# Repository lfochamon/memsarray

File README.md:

# MEMSArray: A prototype MEMS microphone array for the BeagleBone Black

This repository contains a prototype MEMS microphone array cape for the BBB.

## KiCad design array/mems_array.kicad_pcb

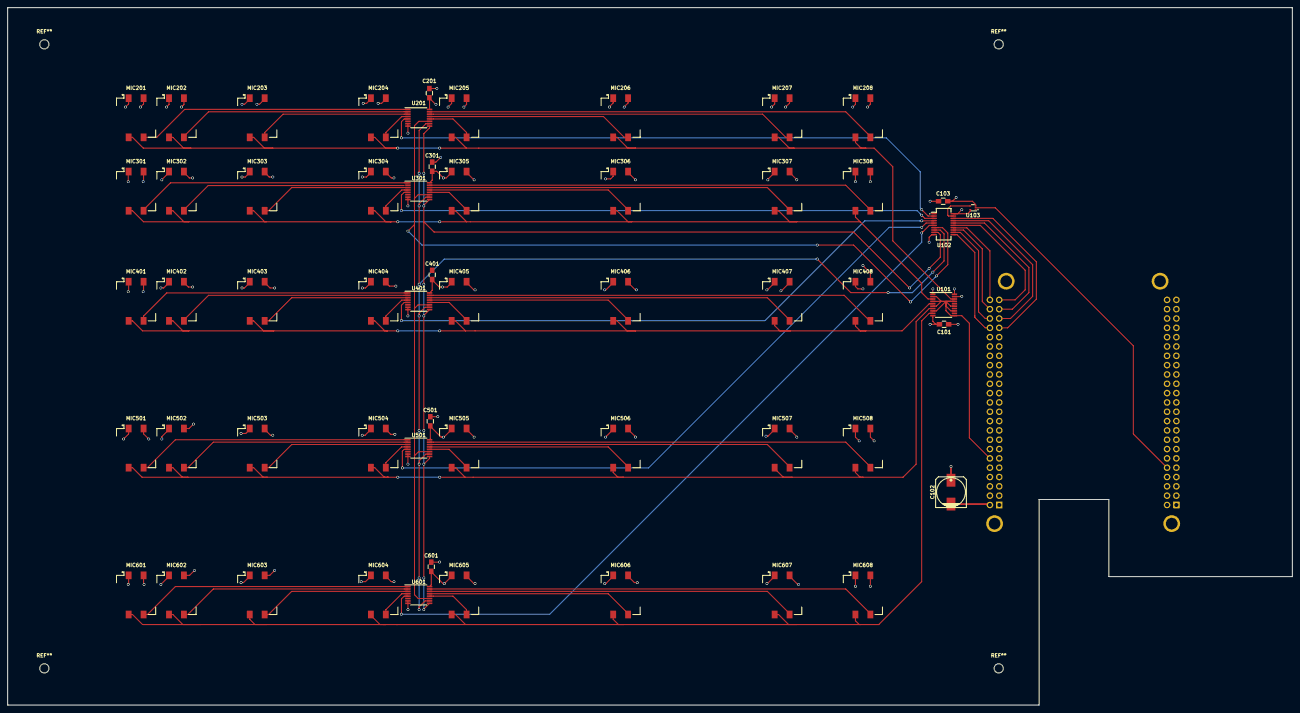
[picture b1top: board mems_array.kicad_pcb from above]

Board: 4 copper layers, 350.0 x 190.0 mm, 57 parts (1 on the bottom side), 66 nets.

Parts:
C101, C103, C201, C301, C401, C501, C601: 1uF; C_0805_HandSoldering
C102: 100uF; c_elec_8x10
MIC201, MIC202, MIC203, MIC204, MIC205, MIC206, MIC207, MIC208, MIC301, MIC302, MIC303, MIC304, MIC305, MIC306, MIC307, MIC308, MIC401, MIC402, MIC403, MIC404, MIC405, MIC406, MIC407, MIC408, MIC501, MIC502, MIC503, MIC504, MIC505, MIC506, MIC507, MIC508, MIC601, MIC602, MIC603, MIC604, MIC605, MIC606, MIC607, MIC608: MIC_MODULE; Mems_Mic_Module
U101: 74AHC244; TSSOP-20_4.4x6.5mm_Pitch0.65mm
U102: 743245; SOP-20_600x175_Pitch0.635
U103: 741G04; SOTFL-5_160x50_Pitch0.5
U104: BEAGLEBONEBLACK; beagleboneblack
U201, U301, U401, U501, U601: SN74CTBLV3251; TSSOP-16_4.4x5mm_Pitch0.65mm

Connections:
/Microphone set A/CLK: MIC201.4, MIC202.4, MIC203.4, MIC204.4, MIC205.4, MIC206.4, MIC207.4, MIC208.4, U101.18
/Microphone set A/OUT: U102.2, U201.5
/Microphone set A/S0: U102.7, U201.11, U301.11, U401.11, U501.11, U601.11
/Microphone set A/S1: U102.8, U201.10, U301.10, U401.10, U501.10, U601.10
/Microphone set A/S2: U102.9, U201.9, U301.9, U401.9, U501.9, U601.9
/Microphone set B/CLK: MIC301.4, MIC302.4, MIC303.4, MIC304.4, MIC305.4, MIC306.4, MIC307.4, MIC308.4, U101.3
/Microphone set B/OUT: U102.3, U301.5
/Microphone set C/CLK: MIC401.4, MIC402.4, MIC403.4, MIC404.4, MIC405.4, MIC406.4, MIC407.4, MIC408.4, U101.5
/Microphone set C/OUT: U102.4, U401.5
/Microphone set D/CLK: MIC501.4, MIC502.4, MIC503.4, MIC504.4, MIC505.4, MIC506.4, MIC507.4, MIC508.4, U101.7
/Microphone set D/OUT: U102.5, U501.5
/Microphone set E/CLK: MIC601.4, MIC602.4, MIC603.4, MIC604.4, MIC605.4, MIC606.4, MIC607.4, MIC608.4, U101.9
/Microphone set E/OUT: U102.6, U601.5
/PRU0_15: U101.2, U101.4, U101.6, U101.8, U101.11, U101.13, U101.15, U101.17, U104.B12
/PRU1_0: U102.15, U104.B45
/PRU1_1: U102.14, U104.B46
/PRU1_2: U102.16, U104.B43
/PRU1_3: U102.13, U104.B44
/PRU1_4: U102.17, U104.B41
/PRU1_5: U102.12, U104.B42
/PRU1_6: U102.18, U104.B39
/PRU1_7: U102.11, U104.B40
/SYS_RESETn: U103.2, U104.C10
DGND: C101.2, C102.2, C103.2, C201.2, C301.2, C401.2, C501.2, C601.2, MIC201.2, MIC202.2, MIC203.2, MIC204.2, MIC205.2, MIC206.2, MIC207.2, MIC208.2, MIC301.2, MIC302.2, MIC303.2, MIC304.2, MIC305.2, MIC306.2, MIC307.2, MIC308.2, MIC401.2, MIC402.2, MIC403.2, MIC404.2, MIC405.2, MIC406.2, MIC407.2, MIC408.2, MIC501.2, MIC502.2, MIC503.2, MIC504.2, MIC505.2, MIC506.2, MIC507.2, MIC508.2, MIC601.2, MIC602.2, MIC603.2, MIC604.2, MIC605.2, MIC606.2, MIC607.2, MIC608.2, U101.1, U101.10, U101.19, U102.10, U103.3, U104.B1, U104.B2, U104.C1, U104.C2, U104.C43, U104.C44, U104.C45, U104.C46, U201.7, U201.8, U301.7, U301.8, U401.7, U401.8, U501.7, U501.8, U601.7, U601.8
DVDD: C101.1, C102.1, C103.1, C201.1, C301.1, C401.1, C501.1, C601.1, MIC201.1, MIC202.1, MIC203.1, MIC204.1, MIC205.1, MIC206.1, MIC207.1, MIC208.1, MIC301.1, MIC302.1, MIC303.1, MIC304.1, MIC305.1, MIC306.1, MIC307.1, MIC308.1, MIC401.1, MIC402.1, MIC403.1, MIC404.1, MIC405.1, MIC406.1, MIC407.1, MIC408.1, MIC501.1, MIC502.1, MIC503.1, MIC504.1, MIC505.1, MIC506.1, MIC507.1, MIC508.1, MIC601.1, MIC602.1, MIC603.1, MIC604.1, MIC605.1, MIC606.1, MIC607.1, MIC608.1, U101.20, U102.20, U103.5, U104.C3, U104.C4, U201.16, U301.16, U401.16, U501.16, U601.16
unnamed: MIC201.3, U201.1
unnamed: MIC202.3, U201.2
unnamed: MIC203.3, U201.3
unnamed: MIC204.3, U201.4
unnamed: MIC205.3, U201.12
unnamed: MIC206.3, U201.13
unnamed: MIC207.3, U201.14
unnamed: MIC208.3, U201.15
unnamed: MIC301.3, U301.1
unnamed: MIC302.3, U301.2
unnamed: MIC303.3, U301.3
unnamed: MIC304.3, U301.4
unnamed: MIC305.3, U301.12
unnamed: MIC306.3, U301.13
unnamed: MIC307.3, U301.14
unnamed: MIC308.3, U301.15
unnamed: MIC401.3, U401.1
unnamed: MIC402.3, U401.2
unnamed: MIC403.3, U401.3
unnamed: MIC404.3, U401.4
unnamed: MIC405.3, U401.12
unnamed: MIC406.3, U401.13
unnamed: MIC407.3, U401.14
unnamed: MIC408.3, U401.15
unnamed: MIC501.3, U501.1
unnamed: MIC502.3, U501.2
unnamed: MIC503.3, U501.3
unnamed: MIC504.3, U501.4
unnamed: MIC505.3, U501.12
unnamed: MIC506.3, U501.13
unnamed: MIC507.3, U501.14
unnamed: MIC508.3, U501.15
unnamed: MIC601.3, U601.1
unnamed: MIC602.3, U601.2
unnamed: MIC603.3, U601.3
unnamed: MIC604.3, U601.4
unnamed: MIC605.3, U601.12
unnamed: MIC606.3, U601.13
unnamed: MIC607.3, U601.14
unnamed: MIC608.3, U601.15
unnamed: U102.19, U103.4

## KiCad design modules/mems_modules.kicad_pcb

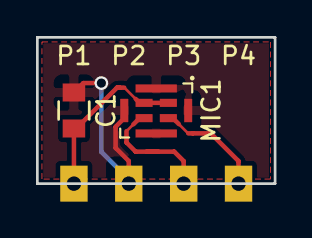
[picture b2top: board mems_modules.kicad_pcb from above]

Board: 2 copper layers, 13.2 x 8.1 mm, 6 parts (0 on the bottom side), 4 nets.

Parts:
C1: 1uF; C_0805
MIC1: MEMS_MIC; Mic-MEMS_Top_8_pins
P1, P2, P3, P4: CASTELLATED_PAD; Castellated_Pad

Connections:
/CLK: MIC1.3, P3.1
/OUT: MIC1.4, P4.1
DGND: C1.2, MIC1.5, P2.1
DVDD: C1.1, MIC1.1, MIC1.2, P1.1

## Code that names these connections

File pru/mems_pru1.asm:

; Pin definitions
CLK                 .set    5       ; PRU1_5 GPIO2_11 P8_42
MIC1                .set    3       ; PRU1_3 GPIO2_9  P8_44
MIC2                .set    1       ; PRU1_1 GPIO2_7  P8_46

; Output clock frequency settings (2 instructions per loop)
CLK_1M              .set    50      ; Half-cycle = 500 ns => fCLK = 1 MHz
CLK_2M4             .set    21      ; Half-cycle = 210 ns => fCLK = 2.38 MHz
CLK_3M072           .set    16      ; Half-cycle = 160 ns => fCLK = 3.125 MHz

CLK_DELAY           .set    CLK_2M4

; Interrupt
PRU_INT_VALID       .set    32
PRU0_PRU1_INTERRUPT .set    1       ; PRU_EVTOUT_
PRU1_PRU0_INTERRUPT .set    2       ; PRU_EVTOUT_
PRU0_ARM_INTERRUPT  .set    3       ; PRU_EVTOUT_0
PRU1_ARM_INTERRUPT  .set    4       ; PRU_EVTOUT_1
ARM_PRU0_INTERRUPT  .set    5       ; PRU_EVTOUT_
ARM_PRU1_INTERRUPT  .set    6       ; PRU_EVTOUT_

; Name PRU register banks
XFR_BANK0           .set    10
XFR_BANK1           .set    11
XFR_BANK2           .set    12
XFR_PRU             .set    14


;*******************
; MEMS ARRAY macros
;*******************
NOP .macro
        MOV r0, r0
    .endm


LBIT    .macro  lbit_reg1, lbit_bit1, lbit_reg2, lbit_bit2
            QBBS    high?, lbit_reg1, lbit_bit1
            CLR     lbit_reg2, lbit_reg2, lbit_bit2
            QBA     end?
high?:      SET     lbit_reg2, lbit_reg2, lbit_bit2
            NOP
end?:
        .endm


MEMS_READ_REG   .macro  mems_read_fullreg_reg
        JAL     r27.w0, mems_read_byte              ; Call mems_read_byte (2 clock)
        MOV     :mems_read_fullreg_reg:.b3, r27.b2  ; Save byte (1 clock)
        LDI32   r29, CLK_DELAY-4                    ; Call wait function (2 clocks)
        JAL     r28.w0, clk_wait

        JAL     r27.w0, mems_read_byte              ; Call mems_read_byte (2 clock)
        MOV     :mems_read_fullreg_reg:.b2, r27.b2  ; Save byte (1 clock)
        LDI32   r29, CLK_DELAY-4                    ; Call wait function (2 clocks)
        JAL     r28.w0, clk_wait

        JAL     r27.w0, mems_read_byte              ; Call mems_read_byte (2 clock)
        MOV     :mems_read_fullreg_reg:.b1, r27.b2  ; Save byte (1 clock)
        LDI32   r29, CLK_DELAY-4                    ; Call wait function (2 clocks)
        JAL     r28.w0, clk_wait

        JAL     r27.w0, mems_read_byte              ; Call mems_read_byte (2 clock)
        MOV     :mems_read_fullreg_reg:.b0, r27.b2  ; Save byte (1 clock)
        LDI32   r29, CLK_DELAY-4                    ; Call wait function (2 clocks)
        JAL     r28.w0, clk_wait
    .endm


; Code starts here
    .text
    .retain
    .retainrefs
    .global         main


;*************************
; MEMS ARRAY main program
;*************************

main:
; Clear clock pin
    SET r30, r30, CLK

; Call wait function
    LDI32       r29, CLK_DELAY
    JAL         r28.w0, clk_wait

; Start of main loop
mainloop:
    MEMS_READ_REG r1
    MEMS_READ_REG r2
    MEMS_READ_REG r3
    MEMS_READ_REG r4
    MEMS_READ_REG r5
    MEMS_READ_REG r6
    MEMS_READ_REG r7
    MEMS_READ_REG r8
    MEMS_READ_REG r9
    MEMS_READ_REG r10
    MEMS_READ_REG r11
    MEMS_READ_REG r12
    MEMS_READ_REG r13
    MEMS_READ_REG r14
    MEMS_READ_REG r15
    MEMS_READ_REG r16
    MEMS_READ_REG r17
    MEMS_READ_REG r18
    MEMS_READ_REG r19
    MEMS_READ_REG r20
    MEMS_READ_REG r21
    MEMS_READ_REG r22
    MEMS_READ_REG r23
    MEMS_READ_REG r24
    MEMS_READ_REG r25

    ; r26 by hand to allow for the data transfer and loop instructions
    JAL     r27.w0, mems_read_byte      ; Call mems_read_byte (2 clock)
    MOV     r26.b3, r27.b2              ; Save byte (1 clock)
    LDI32   r29, CLK_DELAY-4            ; Call wait function (2 clocks)
    JAL     r28.w0, clk_wait

    JAL     r27.w0, mems_read_byte      ; Call mems_read_byte (2 clock)
    MOV     r26.b2, r27.b2              ; Save byte (1 clock)
    LDI32   r29, CLK_DELAY-4            ; Call wait function (2 clocks)
    JAL     r28.w0, clk_wait

    JAL     r27.w0, mems_read_byte      ; Call mems_read_byte (2 clock)
    MOV     r26.b1, r27.b2              ; Save byte (1 clock)
    LDI32   r29, CLK_DELAY-4            ; Call wait function (2 clocks)
    JAL     r28.w0, clk_wait

    JAL     r27.w0, mems_read_byte      ; Call mems_read_byte (2 clock)
    MOV     r26.b0, r27.b2              ; Save byte (1 clock)

    XOUT    XFR_BANK0, &r1, 104                         ; Save to scratch pad (1 clock)
    LDI     r31.b0, PRU_INT_VALID + PRU1_PRU0_INTERRUPT ; Signal PRU0 (1 clock)

    LDI32   r29, CLK_DELAY-5            ; Call wait function (2 clocks)
    JAL     r28.w0, clk_wait

    JMP mainloop        ; [TODO]: make loop conditional (1 clock)
; End of main loop

; Stop PRU (unreachable)
    HALT

;********************************
; MEMS ARRAY auxiliary functions
;********************************

; r29       loop counter (e.g., 'LDI32 r29, clk_wait_delay-2')
; r28.w0    return address
clk_wait:
    SUB     r29, r29, 1
    QBNE    clk_wait, r29, 0

    JMP r28.w0                  ; Return


; r27.b2    saved byte
; r27.w0    return address
mems_read_byte:
    CLR         r30, r30, CLK               ; CLK = 0 (1 clock)
    LDI32       r29, 8                      ; Wait ? ns (7+12 instructions)
    JAL         r28.w0, clk_wait
    LBIT        r31, MIC1, r27.b2, 7        ; Load MIC1 data (3 clocks)
    LBIT        r31, MIC2, r27.b2, 6        ; Load MIC2 data (3 clocks)
    LDI32       r29, CLK_DELAY-6            ; Call wait function (2 clocks)
    JAL         r28.w0, clk_wait
    SET         r30, r30, CLK               ; CLK = 0 (1 clock)
    LDI32       r29, CLK_DELAY-3            ; Call wait function (2 clocks)
    JAL         r28.w0, clk_wait
    NOP

    CLR         r30, r30, CLK               ; CLK = 0 (1 clock)
    LDI32       r29, 8                      ; Wait ? ns (7+12 instructions)
    JAL         r28.w0, clk_wait
    LBIT        r31, MIC1, r27.b2, 5        ; Load MIC1 data (3 clocks)
    LBIT        r31, MIC2, r27.b2, 4        ; Load MIC2 data (3 clocks)
    LDI32       r29, CLK_DELAY-6            ; Call wait function (2 clocks)
    JAL         r28.w0, clk_wait
    SET         r30, r30, CLK               ; CLK = 0 (1 clock)
    LDI32       r29, CLK_DELAY-3            ; Call wait function (2 clocks)
    JAL         r28.w0, clk_wait
    NOP

    CLR         r30, r30, CLK               ; CLK = 0 (1 clock)
    LDI32       r29, 8                      ; Wait ? ns (7+12 instructions)
    JAL         r28.w0, clk_wait
    LBIT        r31, MIC1, r27.b2, 3        ; Load MIC1 data (3 clocks)
    LBIT        r31, MIC2, r27.b2, 2        ; Load MIC2 data (3 clocks)
    LDI32       r29, CLK_DELAY-6            ; Call wait function (2 clocks)
    JAL         r28.w0, clk_wait
    SET         r30, r30, CLK               ; CLK = 0 (1 clock)
    LDI32       r29, CLK_DELAY-3            ; Call wait function (2 clocks)
    JAL         r28.w0, clk_wait
    NOP

    CLR         r30, r30, CLK               ; CLK = 0 (1 clock)
    LDI32       r29, 8                      ; Wait ? ns (7+12 instructions)
    JAL         r28.w0, clk_wait
    LBIT        r31, MIC1, r27.b2, 1        ; Load MIC1 data (3 clocks)
    LBIT        r31, MIC2, r27.b2, 0        ; Load MIC2 data (3 clocks)
    LDI32       r29, CLK_DELAY-6            ; Call wait function (2 clocks)
    JAL         r28.w0, clk_wait
    SET         r30, r30, CLK               ; CLK = 0 (1 clock)

    JMP         r27.w0                      ; Return (1 clock)

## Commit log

2015-07-03 First commit.
2015-07-03 Fix comments.
2015-07-03 Transform CLK_WAIT macro into a function.
    Access CLK_WAIT using JAL-JMP pair instead of using a macro to reduce code size.
2015-07-03 Transform MEMS_READ_BYTE macro into a function.
    Code now fits in PRU1.
2015-07-03 Fix message sizes and number of buffer to TX/RX.
2015-07-03 Fix clock timings.
2015-07-03 Fix input pins definitions in DTO.
    Input pins should not use pull up/down resistors so that the line value does not change value while the mic output is tristated.
2015-07-03 Export data to files on server and client.
2015-07-04 Fix EOL.
2015-07-07 Acquire mic value after falling edge.
    The array is constructed so that L/R select is tied to GND, i.e., so that all mics are DATA1 and push their value on the falling edge of the clock instead of the rising edge.
2015-07-07 Fix code formatting.
2015-07-15 Remove socket code: only save results to local file.
2015-07-15 Remove remaining references to socket code.
2015-07-15 Measure and fix clock timing.
2015-07-15 Fix buffer dump.
2015-07-16 Include P9 alternative pins to DTO.
2015-07-16 Import single mic code for testing.
2015-07-16 MATLAB script to process bit stream.
2015-07-16 Acquire data from two mics.
2015-07-16 Add trace messages throughout program execution.
2015-07-16 Remove wrong unpacking routine.
2015-07-16 Acquire data directly from MATLAB.
2015-07-16 Clean up code and fix coding standards.
2015-12-19 Schematic for the MEMS microphone module.
2015-12-19 Add footprint for castellated pad.
2015-12-19 Generate netlist for PCB.
2015-12-19 Update hole size of castellated pad footprint.
2015-12-19 Create PCB of MEMS microphone module.
2015-12-19 Reduce MEMS mic module.
2015-12-20 Move footprint library to top folder.
2015-12-20 Add MEMS microphone module footprint.
2015-12-20 Fix footprint library path.
2015-12-20 Add MEMS microphone module component.
2015-12-20 Design schematic for the array.
2015-12-21 Change all power pin types to "Power input".
2015-12-21 Annotate and fix ERC errors.
2015-12-21 Generate netlist.
2015-12-21 Add footprints to schematics and generate new netlist.
2015-12-21 Fix MEMS mic module component and regenerate netlist.
2015-12-22 Design array PCB.
    - Several fixes in the schematics to improve pin use and routing.
    - Added 2 power plane layers. Stack up is Signal-GND-VDD-Signal.
    - Missing lib documentation file (.dcm).
2015-12-22 Fix PCB position in the page.
2016-02-21 Move hardware files to /Hardware folder.
2016-02-21 Move host programs to /Software folder.
2016-02-21 Add README.
2016-03-04 Fix unconnected pins.
